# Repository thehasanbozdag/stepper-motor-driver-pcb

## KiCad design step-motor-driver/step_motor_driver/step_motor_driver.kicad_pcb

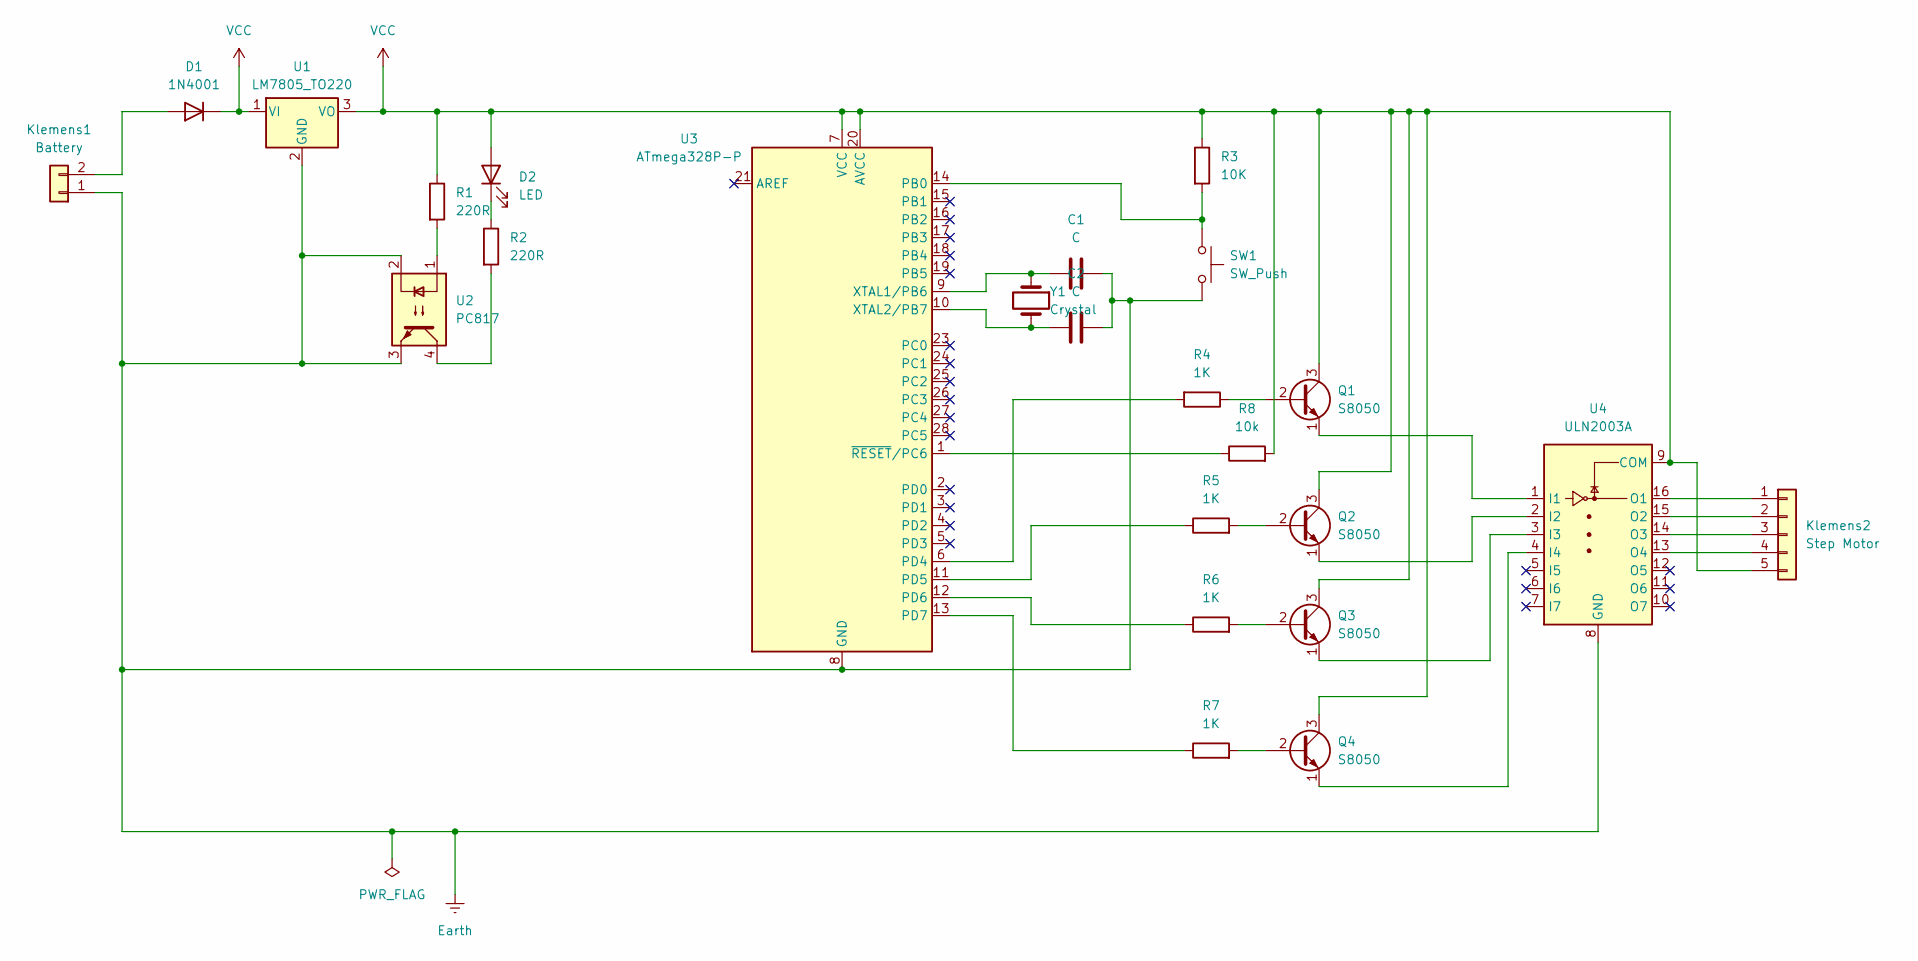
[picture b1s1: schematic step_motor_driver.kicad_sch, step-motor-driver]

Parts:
C1, C2: C; C_Disc_D5.0mm_W2.5mm_P2.50mm
D1: 1N4001; D_DO-41_SOD81_P10.16mm_Horizontal
D2: LED; LED_D8.0mm
Klemens1: Battery; Samtec_HPM-02-01-x-S_Straight_1x02_Pitch5.08mm
Klemens2: Step Motor; Samtec_HPM-05-01-x-S_Straight_1x05_Pitch5.08mm
Q1, Q2, Q3, Q4: S8050; TO-92_Inline
R1, R2: 220R; R_Axial_DIN0207_L6.3mm_D2.5mm_P10.16mm_Horizontal
R3: 10K; R_Axial_DIN0207_L6.3mm_D2.5mm_P10.16mm_Horizontal
R4, R5, R6, R7: 1K; R_Axial_DIN0207_L6.3mm_D2.5mm_P10.16mm_Horizontal
R8: 10k; R_Axial_DIN0207_L6.3mm_D2.5mm_P10.16mm_Horizontal
SW1: SW_Push; SW_PUSH_1P1T_6x3.5mm_H4.3_APEM_MJTP1243
U1: LM7805_TO220; TO-220-3_Vertical
U2: PC817; DIP-4_W7.62mm
U3: ATmega328P-P; DIP-28_W7.62mm
U4: ULN2003A; DIP-16_W7.62mm
Y1: Crystal; Crystal_HC49-4H_Vertical

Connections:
Earth: C1.2, C2.2, Klemens1.1, SW1.2, U1.2 (GND), U2.2, U2.3, U3.8 (GND), U3.22 (GND), U4.8 (GND)
unnamed: D1.2 (A), Klemens1.2
unnamed: D2.1 (K), R2.1
unnamed: Klemens2.1, U4.16 (O1)
unnamed: Klemens2.2, U4.15 (O2)
unnamed: Klemens2.3, U4.14 (O3)
unnamed: Klemens2.4, U4.13 (O4)
unnamed: Q1.2 (B), R4.1
unnamed: Q1.1 (E), U4.1 (I1)
unnamed: Q2.2 (B), R5.2
unnamed: Q2.1 (E), U4.2 (I2)
unnamed: Q3.2 (B), R6.2
unnamed: Q3.1 (E), U4.3 (I3)
unnamed: Q4.2 (B), R7.2
unnamed: Q4.1 (E), U4.4 (I4)
unnamed: R1.2, U2.1
unnamed: R2.2, U2.4
unnamed: R3.2, SW1.1, U3.14 (PB0)
unnamed: R4.2, U3.6 (PD4)
unnamed: R5.1, U3.11 (PD5)
unnamed: R6.1, U3.12 (PD6)
unnamed: R7.1, U3.13 (PD7)
unnamed: C1.1, U3.9 (XTAL1/PB6), Y1.1
unnamed: C2.1, U3.10 (XTAL2/PB7), Y1.2
unnamed: R8.1, U3.1 (~RESET/PC6)
VCC: D1.1 (K), D2.2 (A), Klemens2.5, Q1.3 (C), Q2.3 (C), Q3.3 (C), Q4.3 (C), R1.1, R3.1, R8.2, U1.1 (VI), U1.3 (VO), U3.7 (VCC), U3.20 (AVCC), U4.9 (COM)

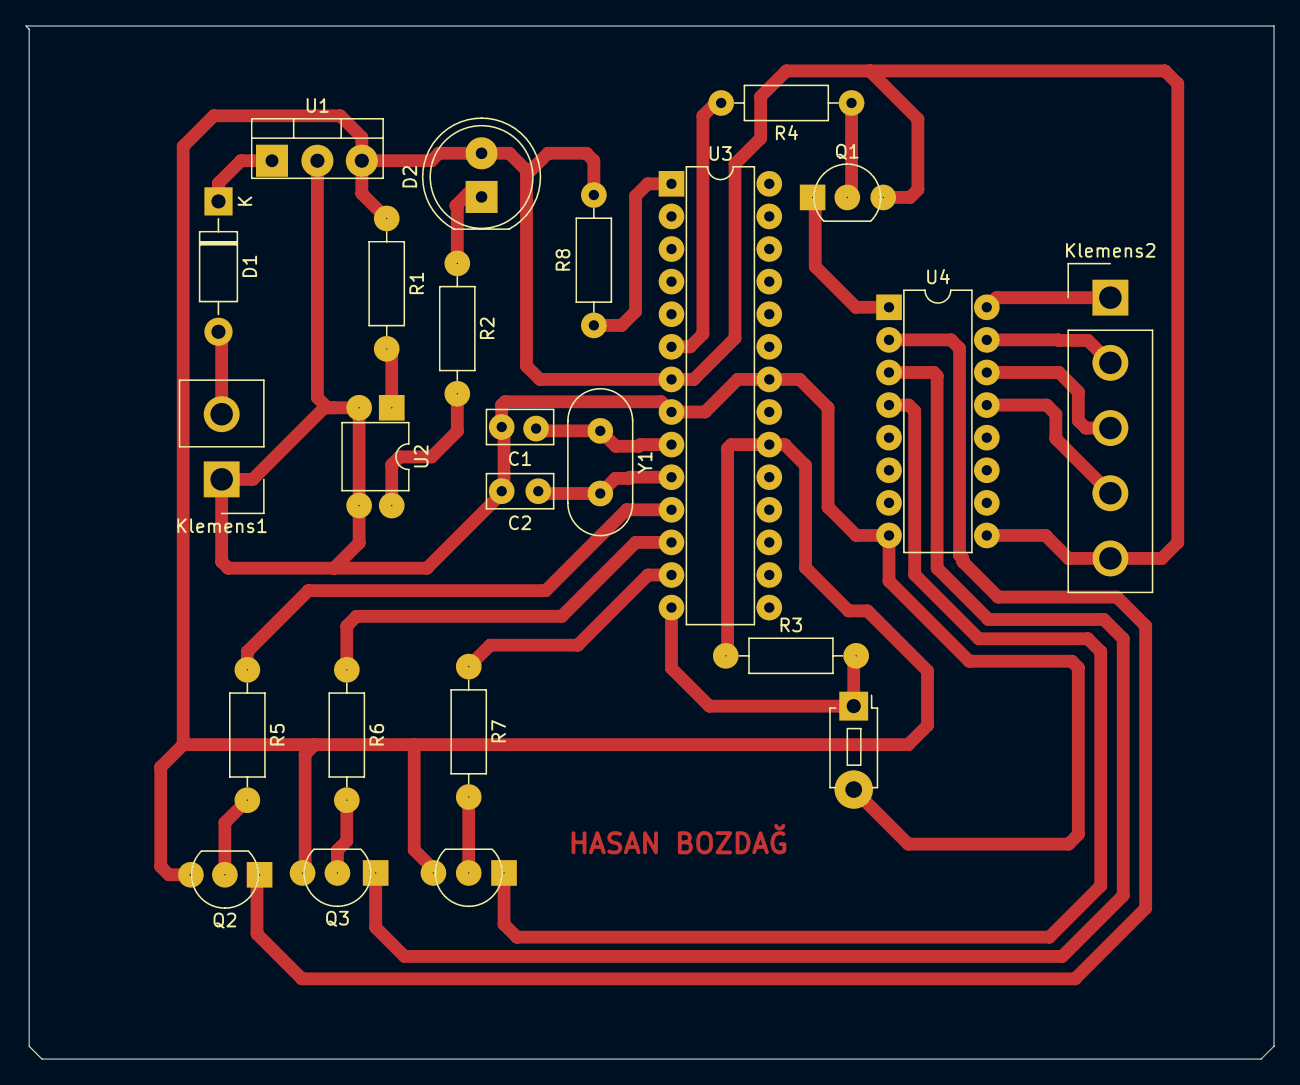
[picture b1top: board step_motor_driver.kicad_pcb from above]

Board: 2 copper layers, 97.2 x 80.5 mm, 24 parts (0 on the bottom side), 26 nets.

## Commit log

2025-05-02 Stepper motor driver design with kicad
    Stepper motor driver design with kicad.
